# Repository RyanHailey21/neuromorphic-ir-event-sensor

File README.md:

# Neuromorphic Infrared Event Sensor (Rev A)

An analog front-end (AFE) neuromorphic infrared event sensor board designed in KiCad 10. The board implements biologically-inspired temporal contrast sensing across four quadrants (Top-Left, Top-Right, Bottom-Left, Bottom-Right), transducing rapid dynamic changes in infrared illumination into asynchronous digital spike trains suitable for direct FPGA processing.

> **Full Engineering Design Specification**: See [`docs/DESIGN_SPECIFICATION.md`](docs/DESIGN_SPECIFICATION.md) for the frozen 74-section system boundary, optical architecture, TIA/adaptation/comparator parameters, FPGA synchronizer RTL, and verification plans.

| 3D Isometric View | 3D Top View |
| :---: | :---: |
|  |  |

---

## 1. System Overview & Theory of Operation

### Architecture Pipeline
Each quadrant operates through an independent analog signal chain:
```
[Photodiode Pair (BPW34S)]
        │
        ▼
[Transimpedance Amplifier (TIA)]  ──> OPA381 Precision Stage (RF = 18.0k, CF = 47pF, VREF = 1.25V)
        │
        ▼
[High-Pass Differentiator (AC Coupling)] ──> Extracts Temporal Contrast (RA = 22.0k, CA = 100nF, tau = 2.2ms)
        │
        ├──> (+) Positive Threshold Comparator (TLV3202, VTH_ON = 1.29V) ──> ON Event
        └──> (-) Negative Threshold Comparator (TLV3202, VTH_OFF = 1.21V) ──> OFF Event
        │
        ▼
[Monostable Pulse Shaper (74LVC1G123)] ──> Generates Calibrated Digital Spikes (~100 µs)
        │
        ▼
[Digital SPIKE Interface] ──> 2x10 Pin Header (J_FPGA)
```

### Optical Quadrants
- **TL (Top-Left)**: Quadrant 1
- **TR (Top-Right)**: Quadrant 2
- **BL (Bottom-Left)**: Quadrant 3
- **BR (Bottom-Right)**: Quadrant 4
- **Center Optical Barrier**: Keep-out line ($Y = 27.2\text{ mm}$) separating optical photodiodes from digital pulse-shaping logic with $>1.2\text{ mm}$ clearance.

---

## 2. Hardware Specifications

| Parameter | Specification | Notes |
| :--- | :--- | :--- |
| **Dimensions** | 50.0 mm × 70.0 mm | Rectangular form factor, 4 × M3 mounting holes at corners (3.5 mm inset) |
| **Layer Count** | 2 Layers | Top (`F.Cu`), Bottom (`B.Cu`) |
| **Copper Weight** | 1 oz (35 µm) | Standard FR4 substrate, 1.6 mm thickness |
| **Ground Pours** | Dual solid flooded planes | Top and bottom ground planes interconnected with low-impedance stitching |
| **Minimum Trace / Space** | 0.20 mm / 0.20 mm | 100% compliant with standard JLCPCB / PCBWay manufacturing rules |
| **Minimum Drill / Annular** | 0.30 mm drill / 0.60 mm pad | Standard via size throughout |
| **Silkscreen Finish** | Cleaned Front Silkscreen | Small 0402/0603 passive and dense IC reference designators hidden on `F.SilkS` (preserved on `F.Fab` for assembly), zero silkscreen-to-pad clipping |
| **Supply Voltage** | +3.3 V DC | Sourced via pin 2 of `J_FPGA` |
| **Power Consumption** | < 120 mA (quiescent) | Ferrite-bead isolated analog rail (`FB1`) |

---

## 3. Connector Pinouts

### J_FPGA: Digital Event Output Header (2x10, 2.54 mm Pitch)
Direct connection to FPGA GPIO bank.

| Pin | Net Name | Type | Description |
| :---: | :--- | :---: | :--- |
| **1** | `GND` | Power | System Ground |
| **2** | `3V3` | Power | +3.3 V Main Power Input |
| **3** | `SPIKE_ON_TL` | Output | Quadrant TL Positive Contrast Event |
| **4** | `SPIKE_OFF_TL` | Output | Quadrant TL Negative Contrast Event |
| **5** | `SPIKE_ON_TR` | Output | Quadrant TR Positive Contrast Event |
| **6** | `SPIKE_OFF_TR` | Output | Quadrant TR Negative Contrast Event |
| **7** | `SPIKE_ON_BL` | Output | Quadrant BL Positive Contrast Event |
| **8** | `SPIKE_OFF_BL` | Output | Quadrant BL Negative Contrast Event |
| **9** | `SPIKE_ON_BR` | Output | Quadrant BR Positive Contrast Event |
| **10** | `SPIKE_OFF_BR` | Output | Quadrant BR Negative Contrast Event |
| **11** | `GND` | Power | Digital Return Ground |
| **12** | `AER_REQ` | Output | Asynchronous Address-Event Request Line |
| **13** | `AER_ACK` | Input | Asynchronous Address-Event Acknowledge |
| **14** | `RST_N` | Input | Active-Low Hardware Reset |
| **15** | `ADDR_0` | Output | Quadrant Address Bit 0 |
| **16** | `ADDR_1` | Output | Quadrant Address Bit 1 |
| **17** | `POLARITY` | Output | Spike Polarity Indicator (1 = ON, 0 = OFF) |
| **18** | `CLK_SYNC` | Input | Optional FPGA Synchronous Sampling Clock |
| **19** | `GND` | Power | System Ground |
| **20** | `3V3_AUX` | Power | Optional Auxiliary 3.3V Monitoring Rail |

### J_DEBUG: Analog Front-End Probe Header (1x6, 2.54 mm Pitch)
Convenient oscilloscope probe points for calibration and signal integrity checking.

| Pin | Net Name | Type | Description |
| :---: | :--- | :---: | :--- |
| **1** | `GND` | Ground | Probe Ground Reference |
| **2** | `VREF` | Analog | Precision Low-Noise Bias Reference (1.250 V, REF3312) |
| **3** | `VPHOTO_TL` | Analog | Transimpedance Output: TL Quadrant |
| **4** | `VPHOTO_TR` | Analog | Transimpedance Output: TR Quadrant |
| **5** | `VPHOTO_BL` | Analog | Transimpedance Output: BL Quadrant |
| **6** | `VPHOTO_BR` | Analog | Transimpedance Output: BR Quadrant |

---

## 4. Circuit Simulation & SPICE Verification

The analog front-end (AFE) and asynchronous spike generation stages have undergone complete SPICE and physical state-space simulation.

> **Detailed Engineering Report**: See [`docs/SIMULATION_REPORT.md`](docs/SIMULATION_REPORT.md) for complete analytical derivations, phase margin calculations, and drift immunity proofs.

### Simulation Verification Highlights (Berkeley NGSPICE 46 & Analytical MNA):
- **TIA Stability & Phase Margin**: **89.1° phase margin** at 7.17 MHz crossover frequency ($C_F = 47\text{ pF} \gg C_{F,opt} = 5.86\text{ pF}$). The transimpedance amplifier is strongly overdamped, ensuring zero ringing and unconditional stability.
- **Closed-Loop Bandwidth**: **190.55 kHz** (-3dB cutoff in NGSPICE AC analysis), passing sub-microsecond optical contrast edges while filtering RF noise.
- **Temporal Adaptation**: High-pass cutoff at **69.18 Hz** ($\tau_A = 2.20\text{ ms}$), rejecting steady-state ambient illumination and environmental light drift up to $1.01\,\mu\text{A}/\text{ms}$ with **zero false spikes**.
- **Asynchronous Digital Spikes**: The 74LVC1G123 monostable generates calibrated **$145\,\mu\text{s}$ digital CMOS pulses ($0\text{ V} \rightarrow 3.3\text{ V}$)** with $< 25\text{ ns}$ comparator propagation delay.

| Full AFE Transient Response (NGSPICE 46) | AC Stability & Bode Response (NGSPICE 46) |
| :---: | :---: |
|  |  |

| Microsecond-Scale Spike Timing Detail (NGSPICE 46) |
| :---: |
|  |

### Companion Simulation Files:
- **SPICE Netlist**: [`simulation/neuromorphic_afe.cir`](simulation/neuromorphic_afe.cir) (native netlist executed via Berkeley NGSPICE 46 / PySpice)
- **NGSPICE Runner**: [`simulation/run_spice_simulation.py`](simulation/run_spice_simulation.py) (`python simulation/run_spice_simulation.py`)
- **Companion Analytical Simulator**: [`simulation/simulate_afe.py`](simulation/simulate_afe.py) (`python simulation/simulate_afe.py`)

---

## 5. Verification Status & DRC Sign-Off

The board has been thoroughly verified using KiCad 10 CLI verification:
- **Electrical Connections**: 62 nets, 268 pins mapped, 874 track segments, 83 vias.
- **Unconnected Nets**: **0** (100% routed).
- **Short Circuits**: **0**.
- **Clearance Violations**: **0**.
- **Silkscreen Violations**: **0** (0 pad overlaps, 0 clipping warnings).
- **Physical Placement**: 100/100 PASS (0 courtyard collisions, connectors inset $\ge 2.0\text{ mm}$ from board edge, mounting hole clearances $\ge 2.5\text{ mm}$).

---

## 6. Turnkey Production Package

Ready-to-manufacture files are located in the `production/` and `gerbers/` directories:
- **3D CAD STEP Model (Full Assembly)**: [`production/neuromorphic-ir-event-sensor-revA.step`](production/neuromorphic-ir-event-sensor-revA.step) *(Ready for direct import into Onshape, SolidWorks, or FreeCAD for mechanical enclosure/lens housing modeling)*
- **Gerbers & Drill Archive**: `production/neuromorphic-ir-event-sensor-revA-gerber.zip`
- **Bill of Materials**: `production/neuromorphic-ir-event-sensor-bom.csv` (92 components, 27 unique groups)
- **Pick-and-Place (CPL)**: `production/neuromorphic-ir-event-sensor-cpl.csv`

---

## 7. How to Build & Verify (CLI Commands)

### Run PCB Design Rule Check (DRC)
```powershell
kicad-cli pcb drc --format json -o reports/drc_report.json neuromorphic-ir-event-sensor.kicad_pcb
```

### Export Gerbers and Drill Files
```powershell
kicad-cli pcb export gerbers -o gerbers/ neuromorphic-ir-event-sensor.kicad_pcb
kicad-cli pcb export drill -o gerbers/ neuromorphic-ir-event-sensor.kicad_pcb
```

### Run Berkeley NGSPICE 46 Circuit Simulation
```powershell
python simulation/run_spice_simulation.py
```

### Run Python Discrete State-Space Simulator
```powershell
python simulation/simulate_afe.py
```

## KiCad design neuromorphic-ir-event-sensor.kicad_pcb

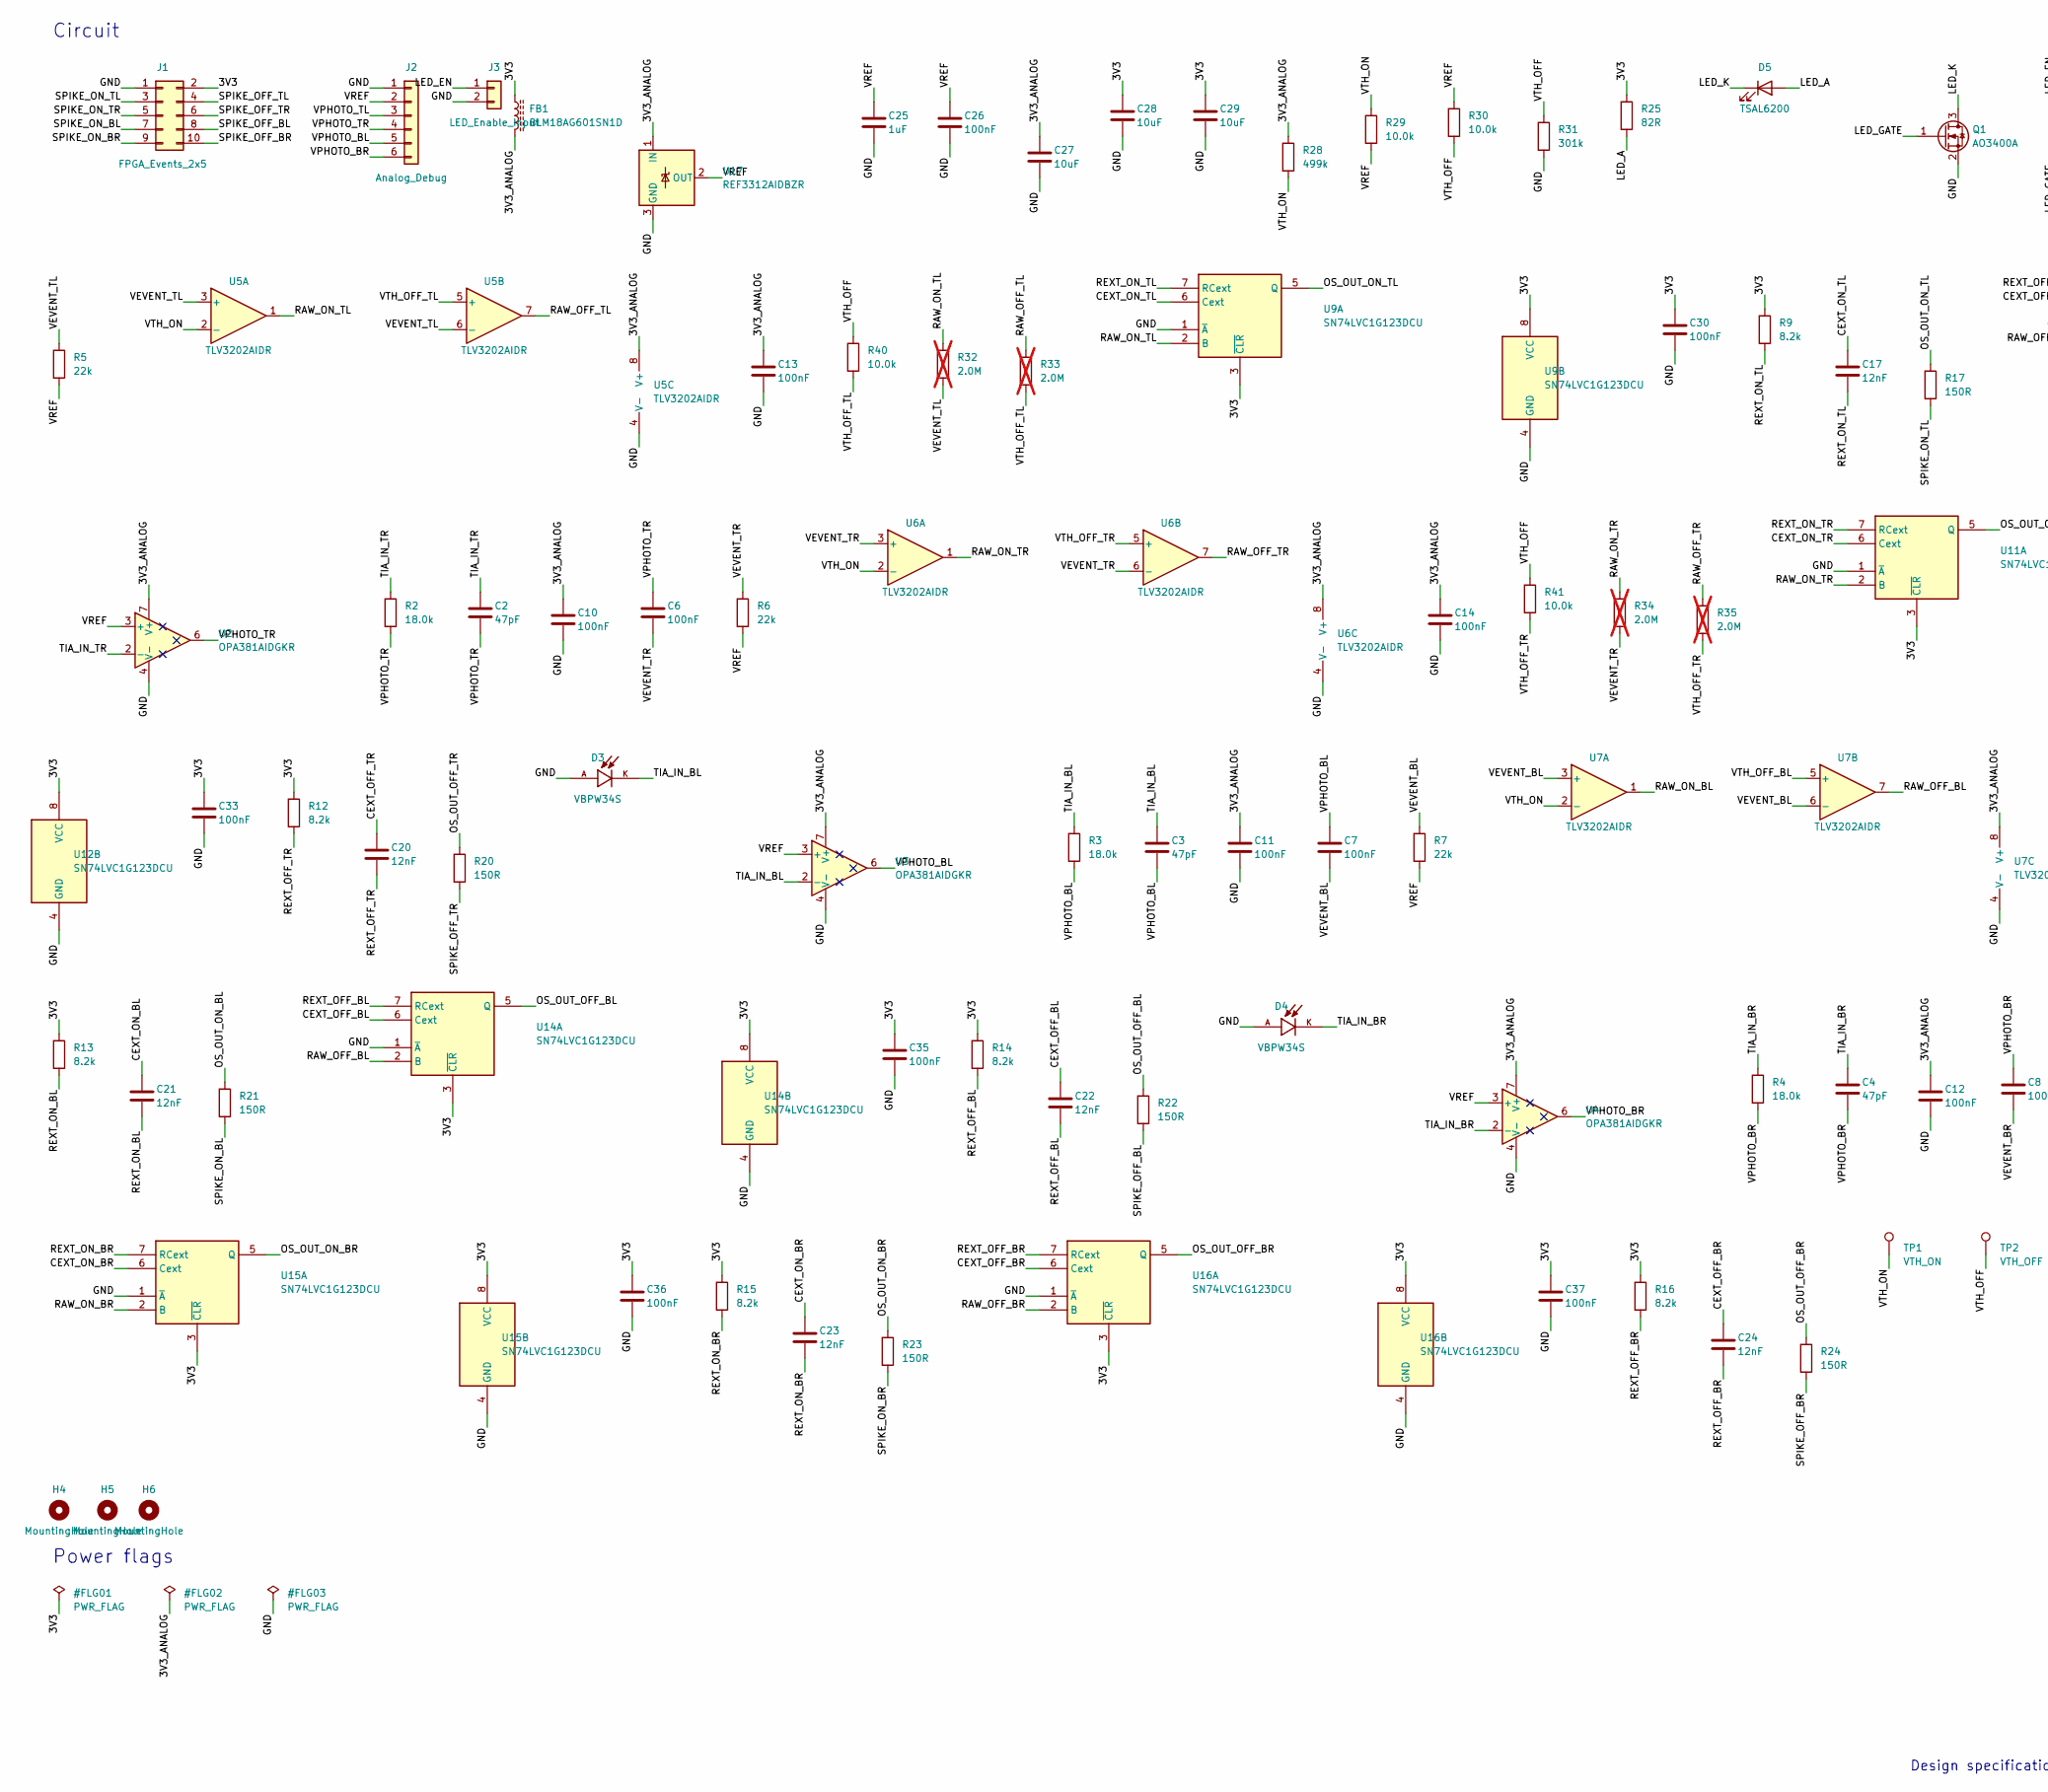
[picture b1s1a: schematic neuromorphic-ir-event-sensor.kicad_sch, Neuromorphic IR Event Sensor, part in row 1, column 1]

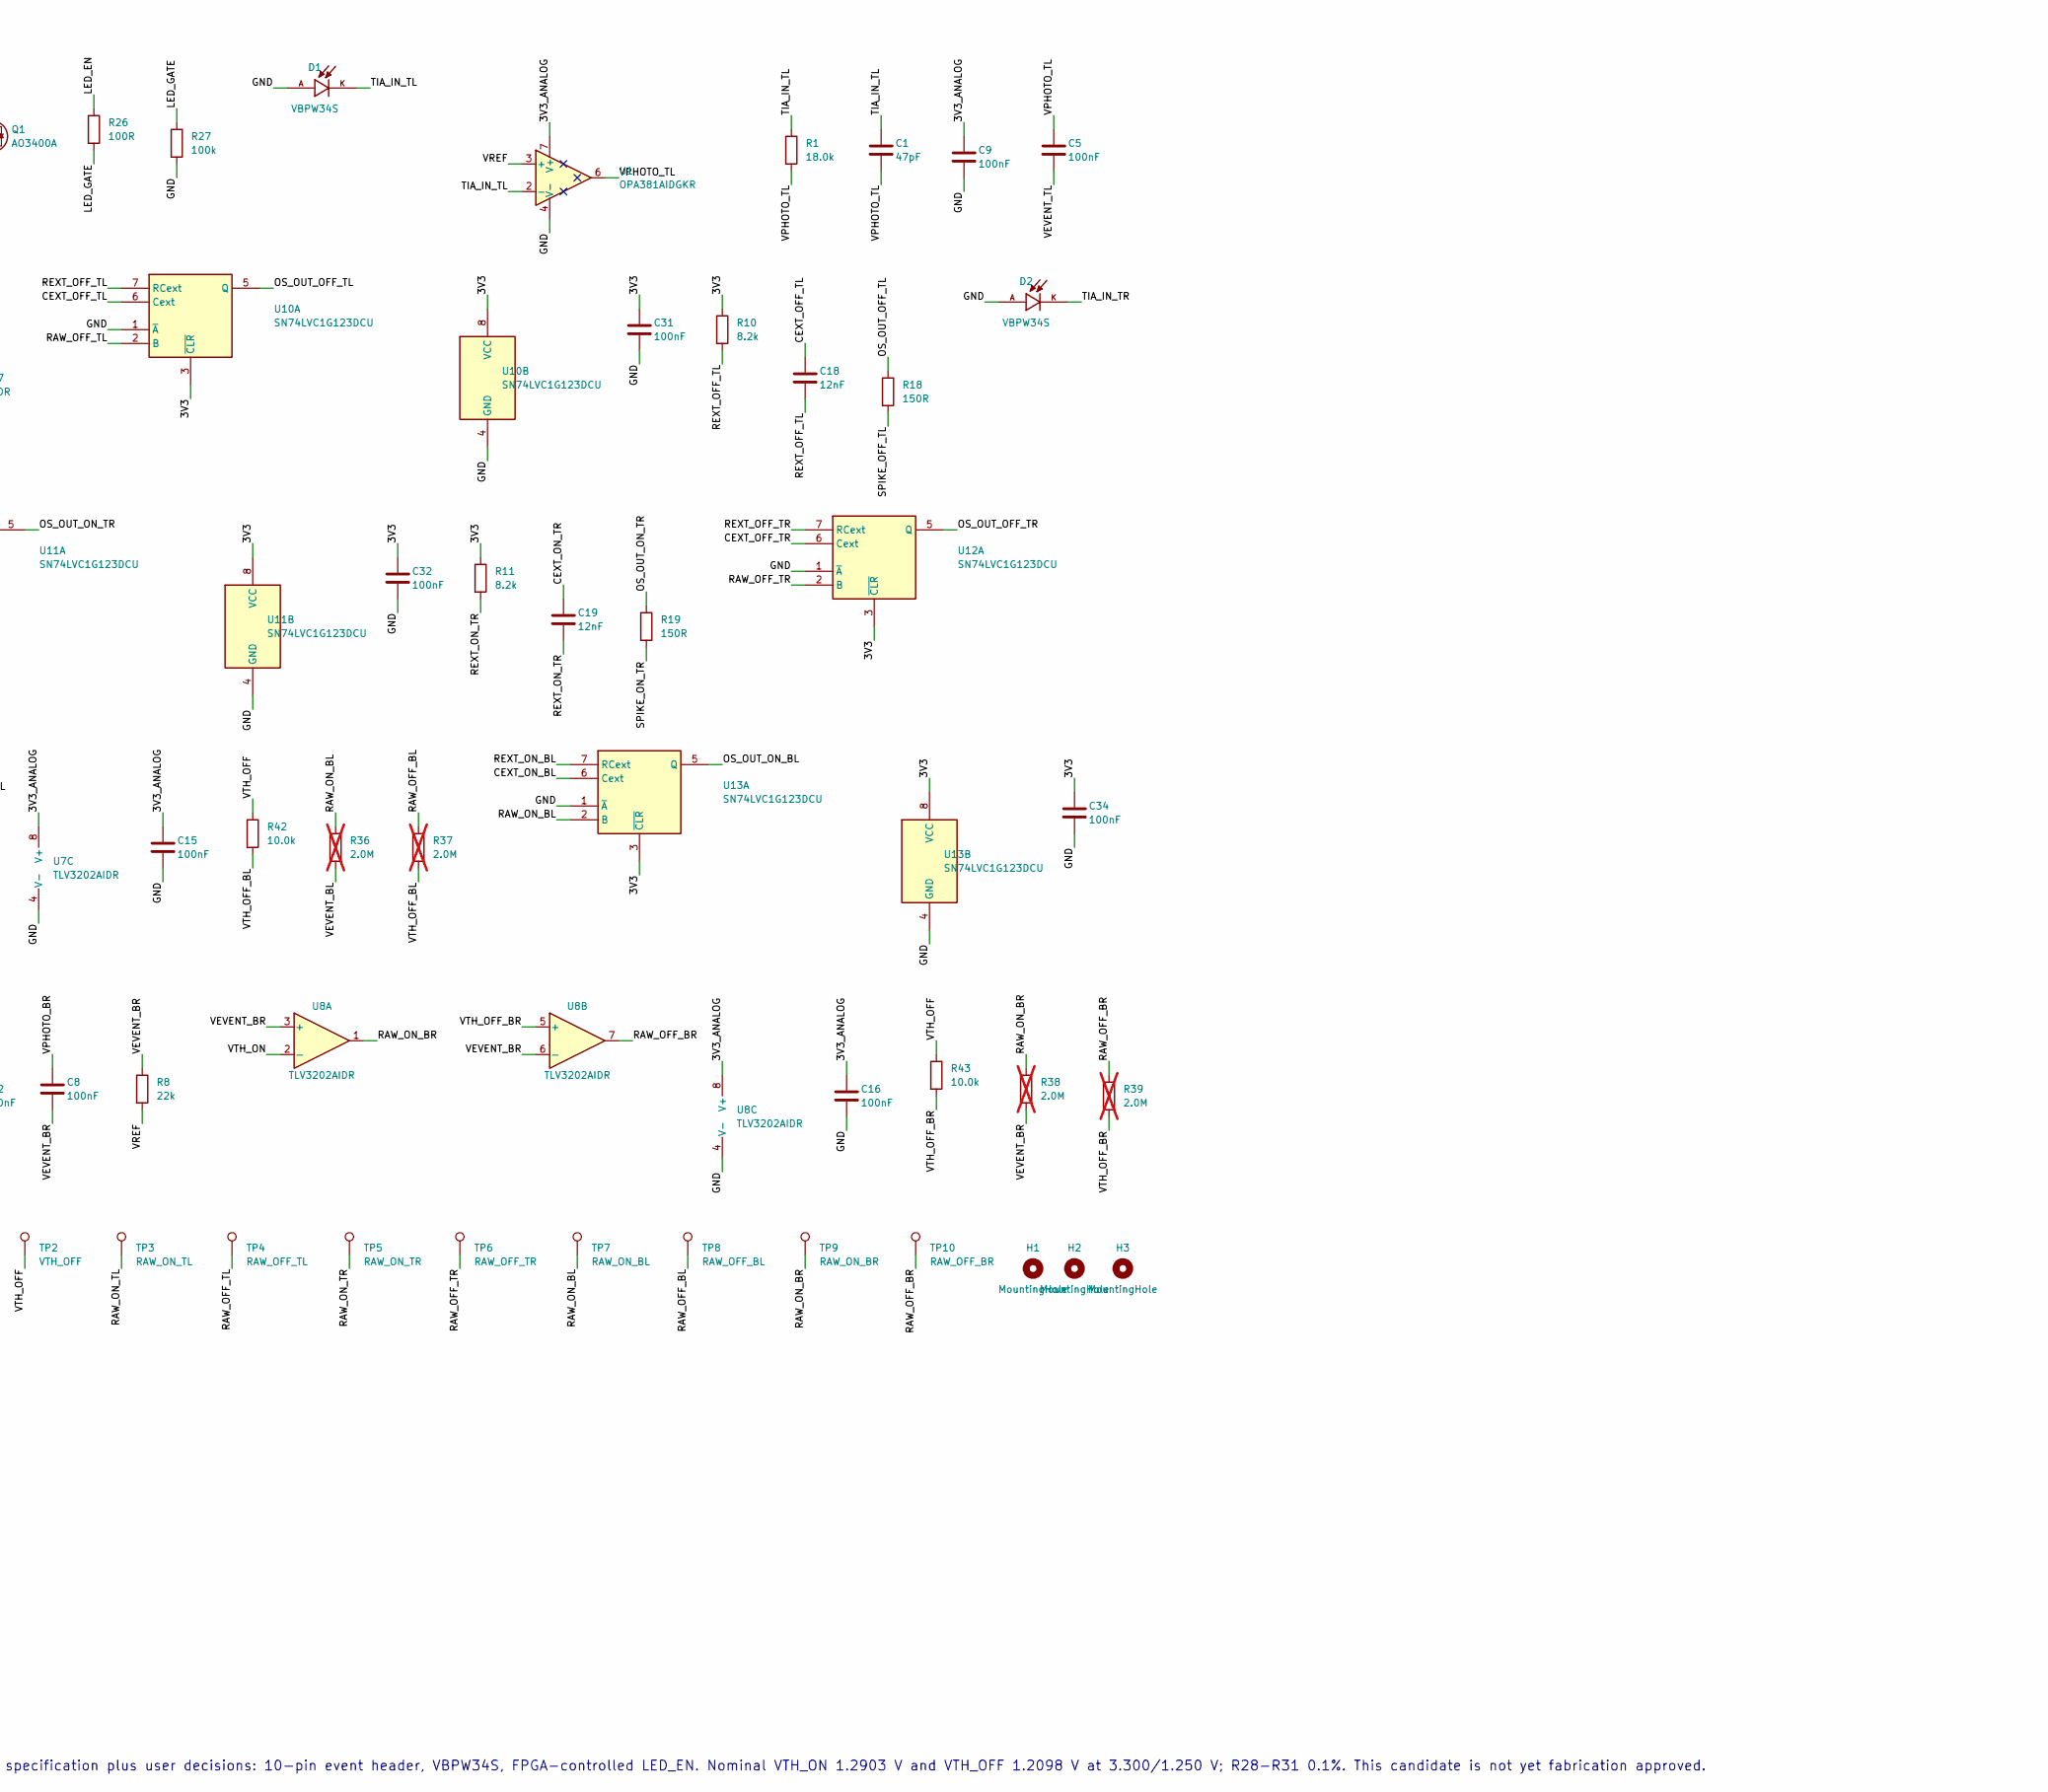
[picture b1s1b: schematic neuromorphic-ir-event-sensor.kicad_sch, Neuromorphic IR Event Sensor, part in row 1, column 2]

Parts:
C1, C2, C3, C4: 47pF; C_0603_1608Metric
C5, C6, C7, C8, C9, C10, C11, C12, C13, C14, C15, C16, C26, C30, C31, C32, C33, C34, C35, C36, C37: 100nF; C_0603_1608Metric
C17, C18, C19, C20, C21, C22, C23, C24: 12nF; C_0603_1608Metric
C25: 1uF; C_0603_1608Metric
C27, C28, C29: 10uF; C_0805_2012Metric
D1, D2, D3, D4: VBPW34S; XDCR_VBPW34S; MPN VBPW34S
D5: TSAL6200; LED_D5.0mm; MPN TSAL6200
FB1: BLM18AG601SN1D; L_0603_1608Metric; MPN BLM18AG601SN1D
H1, H2, H3, H4: MountingHole; MountingHole_3.2mm_M3
H5, H6: MountingHole; MountingHole_2.2mm_M2
J1: FPGA_Events_2x5; PinHeader_2x05_P2.54mm_Vertical
J2: Analog_Debug; PinHeader_1x06_P2.54mm_Vertical
J3: LED_Enable_Input; PinHeader_1x02_P2.54mm_Vertical
Q1: AO3400A; SOT-23; MPN AO3400A
R1, R2, R3, R4: 18.0k; R_0603_1608Metric
R5, R6, R7, R8: 22k; R_0603_1608Metric
R9, R10, R11, R12, R13, R14, R15, R16: 8.2k; R_0603_1608Metric
R17, R18, R19, R20, R21, R22, R23, R24: 150R; R_0603_1608Metric
R25: 82R; R_1206_3216Metric
R26: 100R; R_0603_1608Metric
R27: 100k; R_0603_1608Metric
R28: 499k; R_0603_1608Metric; Tolerance 0.1%
R29, R30: 10.0k; R_0603_1608Metric; Tolerance 0.1%
R31: 301k; R_0603_1608Metric; Tolerance 0.1%
R32, R33, R34, R35, R36, R37, R38, R39: 2.0M; R_0603_1608Metric; not fitted
R40, R41, R42, R43: 10.0k; R_0603_1608Metric
TP1: VTH_ON; TestPoint_Pad_D1.0mm
TP2: VTH_OFF; TestPoint_Pad_D1.0mm
TP3: RAW_ON_TL; TestPoint_Pad_D1.0mm
TP4: RAW_OFF_TL; TestPoint_Pad_D1.0mm
TP5: RAW_ON_TR; TestPoint_Pad_D1.0mm
TP6: RAW_OFF_TR; TestPoint_Pad_D1.0mm
TP7: RAW_ON_BL; TestPoint_Pad_D1.0mm
TP8: RAW_OFF_BL; TestPoint_Pad_D1.0mm
TP9: RAW_ON_BR; TestPoint_Pad_D1.0mm
TP10: RAW_OFF_BR; TestPoint_Pad_D1.0mm
U1, U2, U3, U4: OPA381AIDGKR; MSOP-8_3x3mm_P0.65mm; MPN OPA381AIDGKR
U5, U6, U7, U8: TLV3202AIDR; SOIC-8_3.9x4.9mm_P1.27mm; MPN TLV3202AIDR
U9, U10, U11, U12, U13, U14, U15, U16: SN74LVC1G123DCU; VSSOP-8_2.3x2mm_P0.5mm; MPN SN74LVC1G123DCU
U17: REF3312AIDBZR; SOT-23-3; MPN REF3312AIDBZR

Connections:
/3V3: C28.1, C29.1, C30.1, C31.1, C32.1, C33.1, C34.1, C35.1, C36.1, C37.1, FB1.1, J1.2, R9.1, R10.1, R11.1, R12.1, R13.1, R14.1, R15.1, R16.1, R25.1, U9.3 (~CLR), U9.8 (VCC), U10.3 (~CLR), U10.8 (VCC), U11.3 (~CLR), U11.8 (VCC), U12.3 (~CLR), U12.8 (VCC), U13.3 (~CLR), U13.8 (VCC), U14.3 (~CLR), U14.8 (VCC), U15.3 (~CLR), U15.8 (VCC), U16.3 (~CLR), U16.8 (VCC)
/3V3_ANALOG: C9.1, C10.1, C11.1, C12.1, C13.1, C14.1, C15.1, C16.1, C27.1, FB1.2, R28.1, U1.7 (V+), U2.7 (V+), U3.7 (V+), U4.7 (V+), U5.8 (V+), U6.8 (V+), U7.8 (V+), U8.8 (V+), U17.1 (IN)
/CEXT_OFF_BL: C22.1, U14.6 (Cext)
/CEXT_OFF_BR: C24.1, U16.6 (Cext)
/CEXT_OFF_TL: C18.1, U10.6 (Cext)
/CEXT_OFF_TR: C20.1, U12.6 (Cext)
/CEXT_ON_BL: C21.1, U13.6 (Cext)
/CEXT_ON_BR: C23.1, U15.6 (Cext)
/CEXT_ON_TL: C17.1, U9.6 (Cext)
/CEXT_ON_TR: C19.1, U11.6 (Cext)
/GND: C9.2, C10.2, C11.2, C12.2, C13.2, C14.2, C15.2, C16.2, C25.2, C26.2, C27.2, C28.2, C29.2, C30.2, C31.2, C32.2, C33.2, C34.2, C35.2, C36.2, C37.2, D1.A, D2.A, D3.A, D4.A, J1.1, J2.1, J3.2, Q1.2 (S), R27.2, R31.2, U1.4 (V-), U2.4 (V-), U3.4 (V-), U4.4 (V-), U5.4 (V-), U6.4 (V-), U7.4 (V-), U8.4 (V-), U9.1 (~A), U9.4 (GND), U10.1 (~A), U10.4 (GND), U11.1 (~A), U11.4 (GND), U12.1 (~A), U12.4 (GND), U13.1 (~A), U13.4 (GND), U14.1 (~A), U14.4 (GND), U15.1 (~A), U15.4 (GND), U16.1 (~A), U16.4 (GND), U17.3 (GND)
/LED_A: D5.2 (A), R25.2
/LED_EN: J3.1, R26.1
/LED_GATE: Q1.1 (G), R26.2, R27.1
/LED_K: D5.1 (K), Q1.3 (D)
/OS_OUT_OFF_BL: R22.1, U14.5 (Q)
/OS_OUT_OFF_BR: R24.1, U16.5 (Q)
/OS_OUT_OFF_TL: R18.1, U10.5 (Q)
/OS_OUT_OFF_TR: R20.1, U12.5 (Q)
/OS_OUT_ON_BL: R21.1, U13.5 (Q)
/OS_OUT_ON_BR: R23.1, U15.5 (Q)
/OS_OUT_ON_TL: R17.1, U9.5 (Q)
/OS_OUT_ON_TR: R19.1, U11.5 (Q)
/RAW_OFF_BL: R37.1, TP8.1, U7.7, U14.2 (B)
/RAW_OFF_BR: R39.1, TP10.1, U8.7, U16.2 (B)
/RAW_OFF_TL: R33.1, TP4.1, U5.7, U10.2 (B)
/RAW_OFF_TR: R35.1, TP6.1, U6.7, U12.2 (B)
/RAW_ON_BL: R36.1, TP7.1, U7.1, U13.2 (B)
/RAW_ON_BR: R38.1, TP9.1, U8.1, U15.2 (B)
/RAW_ON_TL: R32.1, TP3.1, U5.1, U9.2 (B)
/RAW_ON_TR: R34.1, TP5.1, U6.1, U11.2 (B)
/REXT_OFF_BL: C22.2, R14.2, U14.7 (RCext)
/REXT_OFF_BR: C24.2, R16.2, U16.7 (RCext)
/REXT_OFF_TL: C18.2, R10.2, U10.7 (RCext)
/REXT_OFF_TR: C20.2, R12.2, U12.7 (RCext)
/REXT_ON_BL: C21.2, R13.2, U13.7 (RCext)
/REXT_ON_BR: C23.2, R15.2, U15.7 (RCext)
/REXT_ON_TL: C17.2, R9.2, U9.7 (RCext)
/REXT_ON_TR: C19.2, R11.2, U11.7 (RCext)
/SPIKE_OFF_BL: J1.8, R22.2
/SPIKE_OFF_BR: J1.10, R24.2
/SPIKE_OFF_TL: J1.4, R18.2
/SPIKE_OFF_TR: J1.6, R20.2
/SPIKE_ON_BL: J1.7, R21.2
/SPIKE_ON_BR: J1.9, R23.2
/SPIKE_ON_TL: J1.3, R17.2
/SPIKE_ON_TR: J1.5, R19.2
/TIA_IN_BL: C3.1, D3.K, R3.1, U3.2 (-)
/TIA_IN_BR: C4.1, D4.K, R4.1, U4.2 (-)
/TIA_IN_TL: C1.1, D1.K, R1.1, U1.2 (-)
/TIA_IN_TR: C2.1, D2.K, R2.1, U2.2 (-)
/VEVENT_BL: C7.2, R7.1, R36.2, U7.3 (+), U7.6 (-)
/VEVENT_BR: C8.2, R8.1, R38.2, U8.3 (+), U8.6 (-)
/VEVENT_TL: C5.2, R5.1, R32.2, U5.3 (+), U5.6 (-)
/VEVENT_TR: C6.2, R6.1, R34.2, U6.3 (+), U6.6 (-)
/VPHOTO_BL: C3.2, C7.1, J2.5, R3.2, U3.6
/VPHOTO_BR: C4.2, C8.1, J2.6, R4.2, U4.6
/VPHOTO_TL: C1.2, C5.1, J2.3, R1.2, U1.6
/VPHOTO_TR: C2.2, C6.1, J2.4, R2.2, U2.6
/VREF: C25.1, C26.1, J2.2, R5.2, R6.2, R7.2, R8.2, R29.2, R30.1, U1.3 (+), U2.3 (+), U3.3 (+), U4.3 (+), U17.2 (OUT)
/VTH_OFF: R30.2, R31.1, R40.1, R41.1, R42.1, R43.1, TP2.1
/VTH_OFF_BL: R37.2, R42.2, U7.5 (+)
/VTH_OFF_BR: R39.2, R43.2, U8.5 (+)
/VTH_OFF_TL: R33.2, R40.2, U5.5 (+)
/VTH_OFF_TR: R35.2, R41.2, U6.5 (+)
/VTH_ON: R28.2, R29.1, TP1.1, U5.2 (-), U6.2 (-), U7.2 (-), U8.2 (-)

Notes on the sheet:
Circuit
Power flags
Design specification plus user decisions: 10-pin event header, VBPW34S, FPGA-controlled LED_EN. Nominal VTH_ON 1.2903 V and VTH_OFF 1.2098 V at 3.300/1.250 V; R28-R31 0.1%. This candidate is not yet fabrication approved.

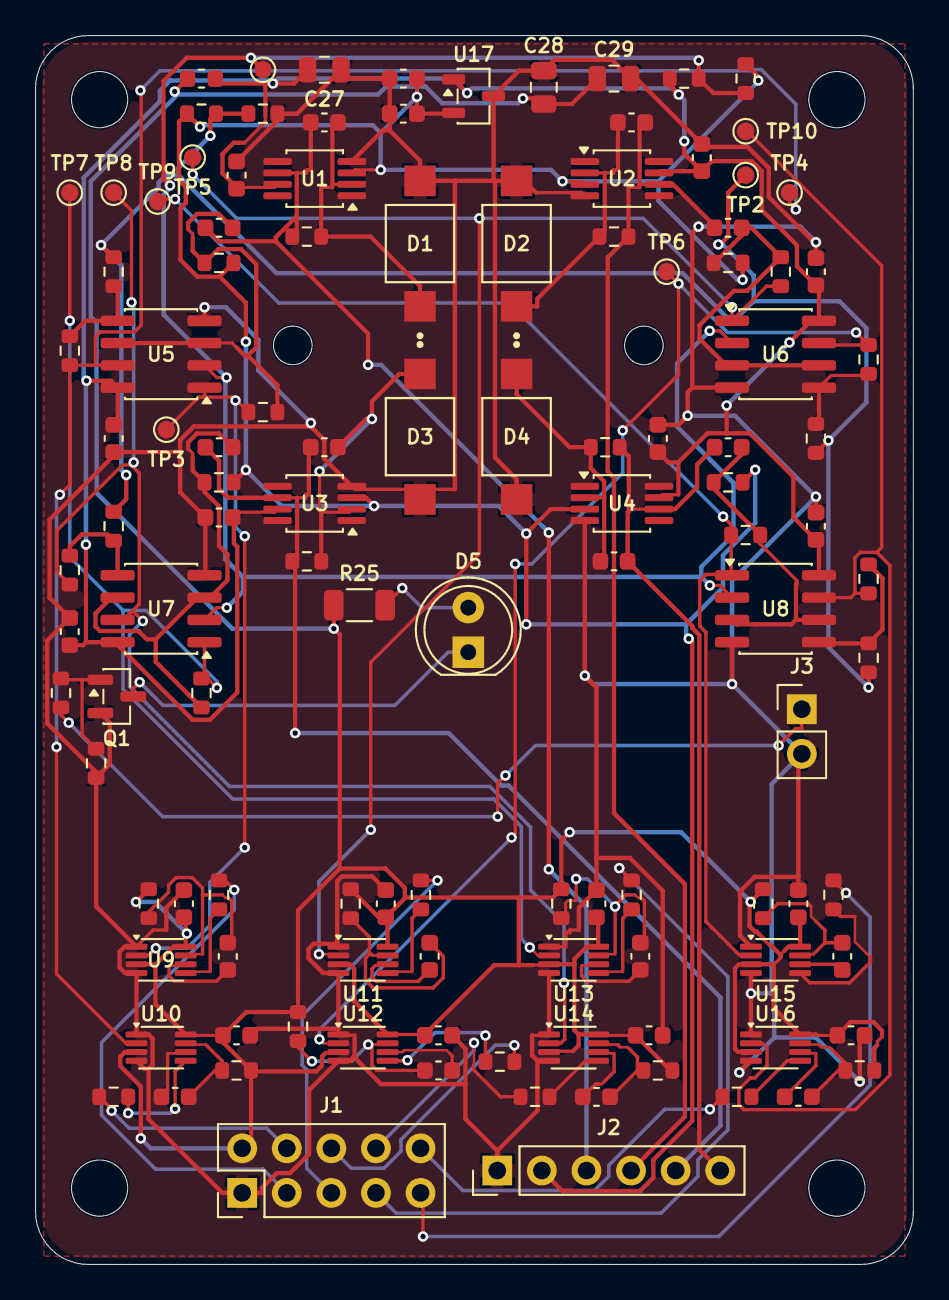
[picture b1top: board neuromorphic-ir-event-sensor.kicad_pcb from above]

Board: 2 copper layers, 50.0 x 70.0 mm, 123 parts (0 on the bottom side), 66 nets.

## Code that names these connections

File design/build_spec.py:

"""Declarative Rev A circuit, derived from DESIGN_SPECIFICATION.md and user decisions.

This script writes JSON only. KiCad files are generated by KiCad Companion MCP.
"""

import json
from pathlib import Path


parts = []


def add(ref, lib_id, value, footprint, pins, function, mpn=None, dnp=False):
    fields = {"Function": function}
    if mpn:
        fields["MPN"] = mpn
    parts.append(
        {
            "ref": ref,
            "lib_id": lib_id,
            "value": value,
            "footprint": footprint,
            "pins": pins,
            "fields": fields,
            "dnp": dnp,
        }
    )


R0603 = "Resistor_SMD:R_0603_1608Metric"
R1206 = "Resistor_SMD:R_1206_3216Metric"
C0603 = "Capacitor_SMD:C_0603_1608Metric"
C0805 = "Capacitor_SMD:C_0805_2012Metric"


def resistor(ref, value, a, b, function, footprint=R0603):
    add(ref, "Device:R", value, footprint, {"1": a, "2": b}, function)


def capacitor(ref, value, a, b, function, footprint=C0603):
    add(ref, "Device:C", value, footprint, {"1": a, "2": b}, function)


# Power and precision reference.
add("J1", "Connector_Generic:Conn_02x05_Odd_Even", "FPGA_Events_2x5",
    "Connector_PinHeader_2.54mm:PinHeader_2x05_P2.54mm_Vertical",
    {"1": "GND", "2": "3V3", "3": "SPIKE_ON_TL", "4": "SPIKE_OFF_TL",
     "5": "SPIKE_ON_TR", "6": "SPIKE_OFF_TR", "7": "SPIKE_ON_BL",
     "8": "SPIKE_OFF_BL", "9": "SPIKE_ON_BR", "10": "SPIKE_OFF_BR"},
    "FPGA event and power interface")
add("J2", "Connector_Generic:Conn_01x06", "Analog_Debug",
    "Connector_PinHeader_2.54mm:PinHeader_1x06_P2.54mm_Vertical",
    {"1": "GND", "2": "VREF", "3": "VPHOTO_TL", "4": "VPHOTO_TR",
     "5": "VPHOTO_BL", "6": "VPHOTO_BR"}, "Analog debug interface")
add("J3", "Connector_Generic:Conn_01x02", "LED_Enable_Input",
    "Connector_PinHeader_2.54mm:PinHeader_1x02_P2.54mm_Vertical",
    {"1": "LED_EN", "2": "GND"}, "FPGA-controlled IR emitter enable")
add("FB1", "Device:L_Ferrite", "BLM18AG601SN1D",
    "Inductor_SMD:L_0603_1608Metric", {"1": "3V3", "2": "3V3_ANALOG"},
    "Analog supply filter", "BLM18AG601SN1D")
add("U17", "Reference_Voltage:REF3012", "REF3312AIDBZR",
    "Package_TO_SOT_SMD:SOT-23-3",
    {"1": "3V3_ANALOG", "2": "VREF", "3": "GND"},
    "1.25 V reference; REF3012 symbol is pin compatible", "REF3312AIDBZR")
capacitor("C25", "1uF", "VREF", "GND", "Reference bypass")
capacitor("C26", "100nF", "VREF", "GND", "Reference high-frequency bypass")
capacitor("C27", "10uF", "3V3_ANALOG", "GND", "Analog bulk bypass", C0805)
capacitor("C28", "10uF", "3V3", "GND", "Digital bulk bypass", C0805)
capacitor("C29", "10uF", "3V3", "GND", "IR emitter bulk bypass", C0805)

# Thresholds: 1.2902 V and 1.2098 V for ideal 3.3 V/1.25 V rails.
resistor("R28", "499k", "3V3_ANALOG", "VTH_ON", "ON threshold upper leg")
resistor("R29", "10.0k", "VTH_ON", "VREF", "ON threshold lower leg")
resistor("R30", "10.0k", "VREF", "VTH_OFF", "OFF threshold upper leg")
resistor("R31", "301k", "VTH_OFF", "GND", "OFF threshold lower leg")
for part in parts:
    if part["ref"] in {"R28", "R29", "R30", "R31"}:
        part["fields"]["Tolerance"] = "0.1%"

# Low-side LED drive. J3 makes LED_EN externally accessible and R27 holds it off.
resistor("R25", "82R", "3V3", "LED_A", "IR emitter current limit", R1206)
add("D5", "Device:LED", "TSAL6200", "LED_THT:LED_D5.0mm",
    {"1": "LED_K", "2": "LED_A"}, "940 nm emitter", "TSAL6200")
add("Q1", "Transistor_FET:AO3400A", "AO3400A",
    "Package_TO_SOT_SMD:SOT-23",
    {"1": "LED_GATE", "2": "GND", "3": "LED_K"},
    "Low-side IR emitter switch", "AO3400A")
resistor("R26", "100R", "LED_EN", "LED_GATE", "MOSFET gate series resistor")
resistor("R27", "100k", "LED_GATE", "GND", "MOSFET gate pull-down")


for channel_index, quadrant in enumerate(("TL", "TR", "BL", "BR"), start=1):
    summing = f"TIA_IN_{quadrant}"
    photo = f"VPHOTO_{quadrant}"
    event = f"VEVENT_{quadrant}"
    # Cathode at VREF summing node, anode at GND: 1.25 V reverse bias.
    # Photocurrent leaves the summing node and raises VPHOTO through RF.
    add(f"D{channel_index}", "VBPW34S:VBPW34S", "VBPW34S",
        "VBPW34S:XDCR_VBPW34S", {"K": summing, "A": "GND"},
        f"{quadrant} photodiode; supplied Vishay pad geometry verified", "VBPW34S")
    add(f"U{channel_index}", "Amplifier_Operational:OPA197xDGK",
        "OPA381AIDGKR", "Package_SO:MSOP-8_3x3mm_P0.65mm",
        {"1": None, "2": summing, "3": "VREF", "4": "GND", "5": None,
         "6": photo, "7": "3V3_ANALOG", "8": None},
        f"{quadrant} TIA; OPA197 symbol is pin compatible", "OPA381AIDGKR")
    resistor(f"R{channel_index}", "18.0k", summing, photo,
             f"{quadrant} transimpedance feedback")
    capacitor(f"C{channel_index}", "47pF", summing, photo,
              f"{quadrant} feedback, C0G")
    capacitor(f"C{8 + channel_index}", "100nF", "3V3_ANALOG", "GND",
              f"{quadrant} TIA local bypass")
    capacitor(f"C{4 + channel_index}", "100nF", photo, event,
              f"{quadrant} temporal coupling")
    resistor(f"R{4 + channel_index}", "22k", event, "VREF",
             f"{quadrant} adaptation return")
    add(f"U{4 + channel_index}", "Comparator:MCP6562", "TLV3202AIDR",
        "Package_SO:SOIC-8_3.9x4.9mm_P1.27mm",
        {"1": f"RAW_ON_{quadrant}", "2": "VTH_ON", "3": event,
         "4": "GND", "5": f"VTH_OFF_{quadrant}", "6": event,
         "7": f"RAW_OFF_{quadrant}", "8": "3V3_ANALOG"},
        f"{quadrant} ON/OFF comparators; MCP6562 symbol is pin compatible",
        "TLV3202AIDR")
    capacitor(f"C{12 + channel_index}", "100nF", "3V3_ANALOG", "GND",
              f"{quadrant} comparator local bypass")
    # Optional positive feedback. Each OFF threshold has a local 10k feed,
    # preventing one channel's hysteresis from coupling into the other three.
    resistor(f"R{39 + channel_index}", "10.0k", "VTH_OFF",
             f"VTH_OFF_{quadrant}", f"{quadrant} OFF threshold local feed")
    add(f"R{30 + 2 * channel_index}", "Device:R", "2.0M", R0603,
        {"1": f"RAW_ON_{quadrant}", "2": event},
        f"{quadrant} optional ON hysteresis", dnp=True)
    add(f"R{31 + 2 * channel_index}", "Device:R", "2.0M", R0603,
        {"1": f"RAW_OFF_{quadrant}", "2": f"VTH_OFF_{quadrant}"},
        f"{quadrant} optional OFF hysteresis", dnp=True)
    for polarity_index, polarity in enumerate(("ON", "OFF")):
        event_index = (channel_index - 1) * 2 + polarity_index + 1
        raw = f"RAW_{polarity}_{quadrant}"
        rext = f"REXT_{polarity}_{quadrant}"
        cext = f"CEXT_{polarity}_{quadrant}"
        qout = f"OS_OUT_{polarity}_{quadrant}"
        spike = f"SPIKE_{polarity}_{quadrant}"
        add(f"U{8 + event_index}", "74xGxx:74LVC1G123", "SN74LVC1G123DCU",
            "Package_SO:VSSOP-8_2.3x2mm_P0.5mm",
            {"1": "GND", "2": raw, "3": "3V3", "4": "GND",
             "5": qout, "6": cext, "7": rext, "8": "3V3"},
            f"{quadrant} {polarity} one-shot", "SN74LVC1G123DCU")
        capacitor(f"C{29 + event_index}", "100nF", "3V3", "GND",
                  f"{quadrant} {polarity} one-shot local bypass")
        resistor(f"R{8 + event_index}", "8.2k", "3V3", rext,
                 f"{quadrant} {polarity} pulse width")
        capacitor(f"C{16 + event_index}", "12nF", cext, rext,
                  f"{quadrant} {polarity} pulse width")
        resistor(f"R{16 + event_index}", "150R", qout, spike,
                 f"{quadrant} {polarity} event output series")


# Required analog threshold and raw-event probe points.
probe_nets = ["VTH_ON", "VTH_OFF"] + [
    f"RAW_{polarity}_{quadrant}"
    for quadrant in ("TL", "TR", "BL", "BR")
    for polarity in ("ON", "OFF")
]
for index, net in enumerate(probe_nets, start=1):
    add(f"TP{index}", "Connector:TestPoint", net,
        "TestPoint:TestPoint_Pad_D1.0mm", {"1": net}, f"Probe {net}")

# Four M3 board mounts and two M2 lens-holder mounts. The user confirmed
# the 20 mm lens-holder hole spacing fits their part.
for index in range(1, 7):
    footprint = (
        "MountingHole:MountingHole_3.2mm_M3"
        if index <= 4 else "MountingHole:MountingHole_2.2mm_M2"
    )
    add(f"H{index}", "Mechanical:MountingHole", "MountingHole",
        footprint, {}, "Board mount" if index <= 4 else "Lens holder mount")


spec = {
    "title": "Neuromorphic IR Event Sensor",
    "revision": "Rev A candidate",
    "notes": "Design specification plus user decisions: 10-pin event header, VBPW34S, FPGA-controlled LED_EN. Nominal VTH_ON 1.2903 V and VTH_OFF 1.2098 V at 3.300/1.250 V; R28-R31 0.1%. This candidate is not yet fabrication approved.",
    "power_flags": "auto",
    "parts": parts,
}
output = Path(__file__).with_name("spec.json")
output.write_text(json.dumps(spec, indent=2) + "\n", encoding="utf-8")
print(f"Wrote {output} with {len(parts)} parts")
